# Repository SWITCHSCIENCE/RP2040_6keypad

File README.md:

# RP2040_6keypad

This repository contains KiCad data for 6keypads using the Switch Science RP2040 breakout board.

[Picossci RP2040 ピッチ変換基板](https://ssci.to/8440)を利用したKiCadサンプルデータのリポジトリです。

## KiCad_Project

KiCadプロジェクトです。回路図PDFを含みます。

## RP2040_breakout_KiCad_Symbol

[Picossci RP2040 ピッチ変換基板](https://ssci.to/8440)のKiCad用回路図シンボルとフットプリントデータです。この基板の販売ページで配布されている物と同じです。

## sample_software/rp2040_6key_pad_example

Raspberry Pi Pico C/C++ SDKを用いた簡単なサンプルソフトウェアです。USBシリアル変換アダプターとして機能し、押されたキーの番号をPCのシリアルポートへ送信します。
さらに押されたキーに対応するLEDが点灯します。簡単なREADME.mdを添付しています。

## qmk_firmware/qmk_configs_for_rp2040_6_keypad

QMK Firmwareをrp2040 6-key padに対応させるための設定ファイルとソースコードを書きました。ソースコード差分のみzipファイルにしています。
ビルド方法などの詳細は中のREADME.mdをご確認ください。
今回は6つのキーをBackspace、Enter、上下左右キーに割り振っています。LEDはCapsLockのLEDインジケーターとして動作します。

## prk_firmware/keymap.rb

PRK Firmware用のキーボード設定ファイルです。[PRK Firmware](https://github.com/picoruby/prk_firmware)のuf2ファイルを書き込み後、このファイルkeymap.rbをコピーしてください。キーマップや挙動を変更する時はこのkeymap.rbを書き換えるだけでいいのでQMK Firmwareに比べて試行が簡単です。
6つのキーには123456の数字を割り当ててあり、14、25、36のキーそれぞれを押すと対応したLEDが光ります。

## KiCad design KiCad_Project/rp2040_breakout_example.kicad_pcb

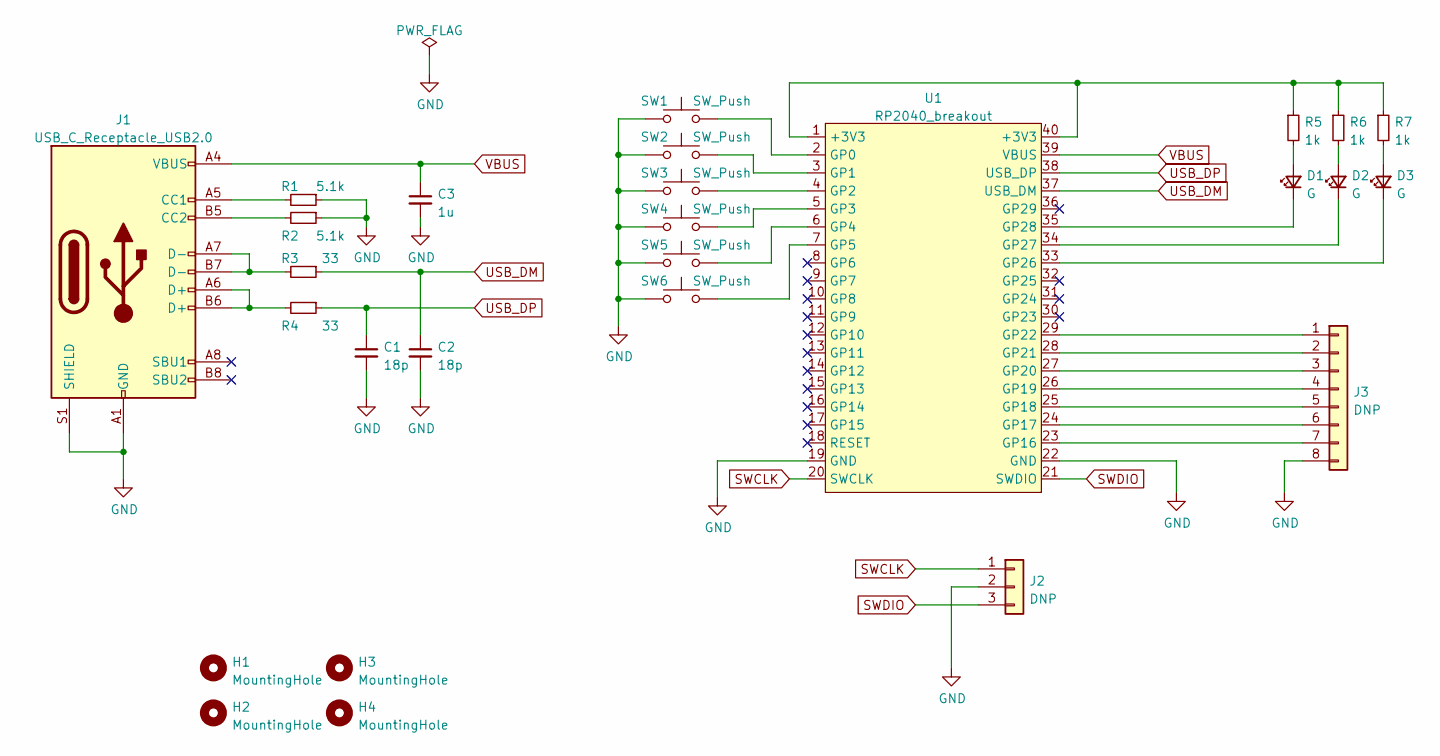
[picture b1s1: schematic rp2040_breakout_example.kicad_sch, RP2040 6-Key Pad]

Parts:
C1, C2: 18p; C_0402_1005Metric
C3: 1u; C_0603_1608Metric
D1, D2, D3: G; LED_0603_1608Metric
H1, H2, H3, H4: MountingHole; MountingHole_3.2mm_M3
J1: USB_C_Receptacle_USB2.0; USB_C_Receptacle_XKB_U262-16XN-4BVC11
J2: DNP; PinHeader_1x03_P2.54mm_Vertical
J3: DNP; PinHeader_1x08_P2.54mm_Vertical
R1, R2: 5.1k; R_0402_1005Metric
R3, R4: 33; R_0402_1005Metric
R5, R6, R7: 1k; R_0402_1005Metric
SW1, SW2, SW3, SW4, SW5, SW6: SW_Push; SW_Cherry_MX_1.00u_PCB
U1: RP2040_breakout; RP2040_Breakout

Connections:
GND: C1.2, C2.2, C3.2, J1.A1 (GND), J1.A12 (GND), J1.B1 (GND), J1.B12 (GND), J1.S1 (SHIELD), J2.2, J3.8, R1.1, R2.1, SW1.1, SW2.1, SW3.1, SW4.1, SW5.1, SW6.1, U1.19 (GND), U1.22 (GND)
unnamed: D1.1 (K), U1.35 (GP28)
unnamed: D1.2 (A), R5.2
unnamed: D2.1 (K), U1.34 (GP27)
unnamed: D2.2 (A), R6.2
unnamed: D3.1 (K), U1.33 (GP26)
unnamed: D3.2 (A), R7.2
unnamed: J1.A5 (CC1), R1.2
unnamed: J1.A6 (D+), J1.B6 (D+), R4.2
unnamed: J1.A7 (D-), J1.B7 (D-), R3.2
unnamed: J1.B5 (CC2), R2.2
unnamed: J3.1, U1.29 (GP22)
unnamed: J3.2, U1.28 (GP21)
unnamed: J3.3, U1.27 (GP20)
unnamed: J3.4, U1.26 (GP19)
unnamed: J3.5, U1.25 (GP18)
unnamed: J3.6, U1.24 (GP17)
unnamed: J3.7, U1.23 (GP16)
unnamed: R5.1, R6.1, R7.1, U1.1 (+3V3), U1.40 (+3V3)
unnamed: SW1.2, U1.2 (GP0)
unnamed: SW2.2, U1.3 (GP1)
unnamed: SW3.2, U1.4 (GP2)
unnamed: SW4.2, U1.5 (GP3)
unnamed: SW5.2, U1.6 (GP4)
unnamed: SW6.2, U1.7 (GP5)
SWCLK: J2.1, U1.20 (SWCLK)
SWDIO: J2.3, U1.21 (SWDIO)
USB_DM: C2.1, R3.1, U1.37 (USB_DM)
USB_DP: C1.1, R4.1, U1.38 (USB_DP)
VBUS: C3.1, J1.A4 (VBUS), J1.A9 (VBUS), J1.B4 (VBUS), J1.B9 (VBUS), U1.39 (VBUS)

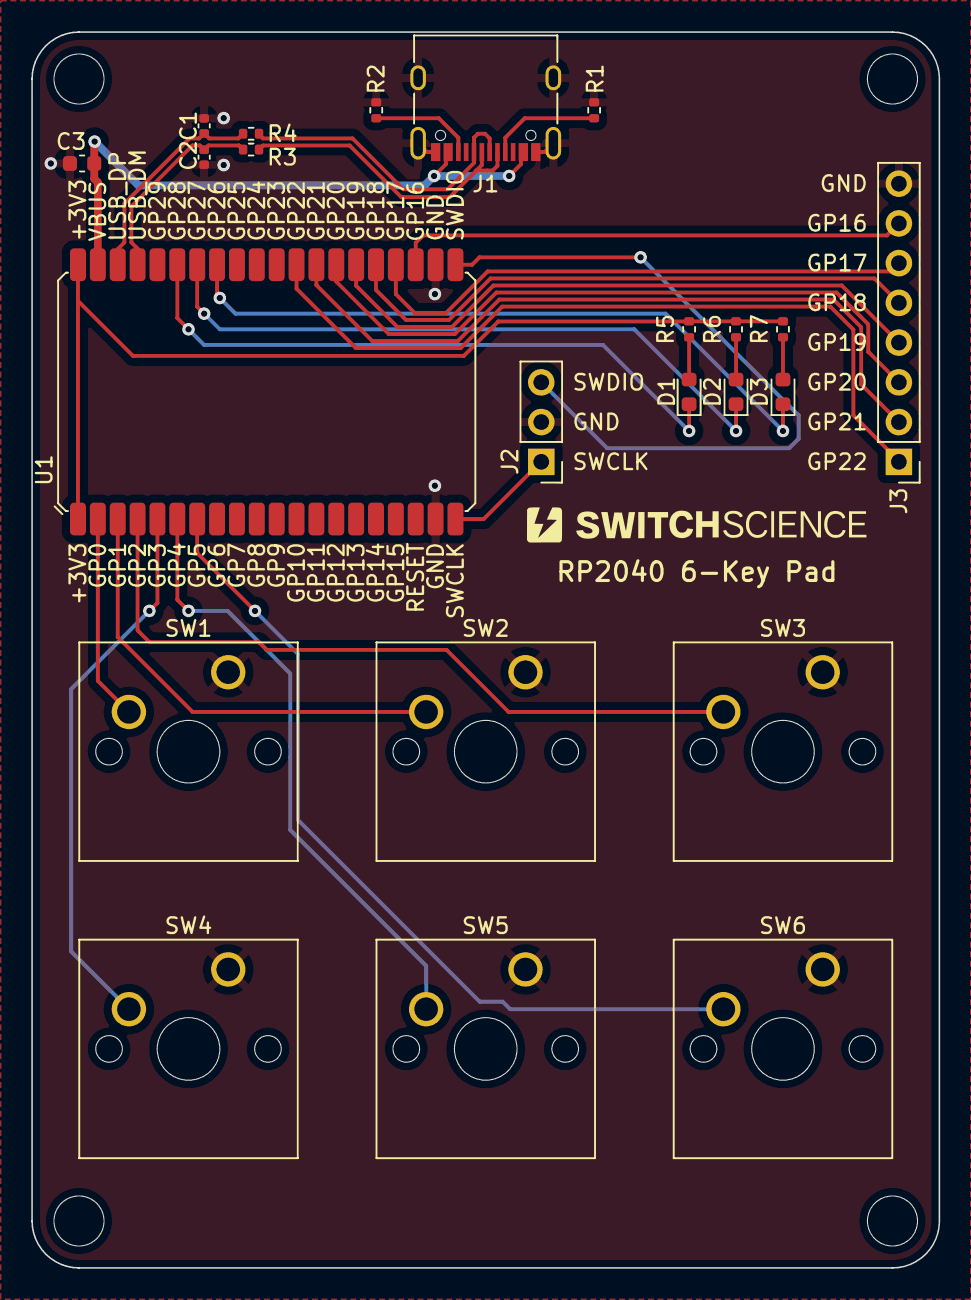
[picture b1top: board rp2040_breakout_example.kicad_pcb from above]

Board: 2 copper layers, 58.0 x 79.0 mm, 27 parts (0 on the bottom side), 30 nets.

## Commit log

2023-08-03 Add a license file.
2023-08-04 Add KiCad symbol.
2025-07-17 Update keymap.rb
    rpk firmware 0.10.0に対応
